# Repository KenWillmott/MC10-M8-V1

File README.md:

# MC10-M8-V1
Basic TRS-80 MC-10 to M8 expansion interface

## Description
Allows one M8 peripheral expansion card to operate from the expansion port on the rear of the TRS-80 MC-10 microcomputer. The circuit decodes an I/O slot at 0xB400-0xB7FF, so any M8 peripheral card will be addressed by the MC-10 at that location, plus any internal offset that the card uses. In order to prevent a hardware bus conflict when accessing those location, the SEL line on the MC-10 interface is activated to disable its internal devices mapped to the same locations.

Note: Gating with the CPU E signal is not performed by the interface card, it is always done on the M8 card. But, this is quite easy to do on the M8 card and some cards can do it without additional logic, since some I/O IC's perform E gating internally (such as 6522 VIA, Motorola MC6850, MC6821 etc.).

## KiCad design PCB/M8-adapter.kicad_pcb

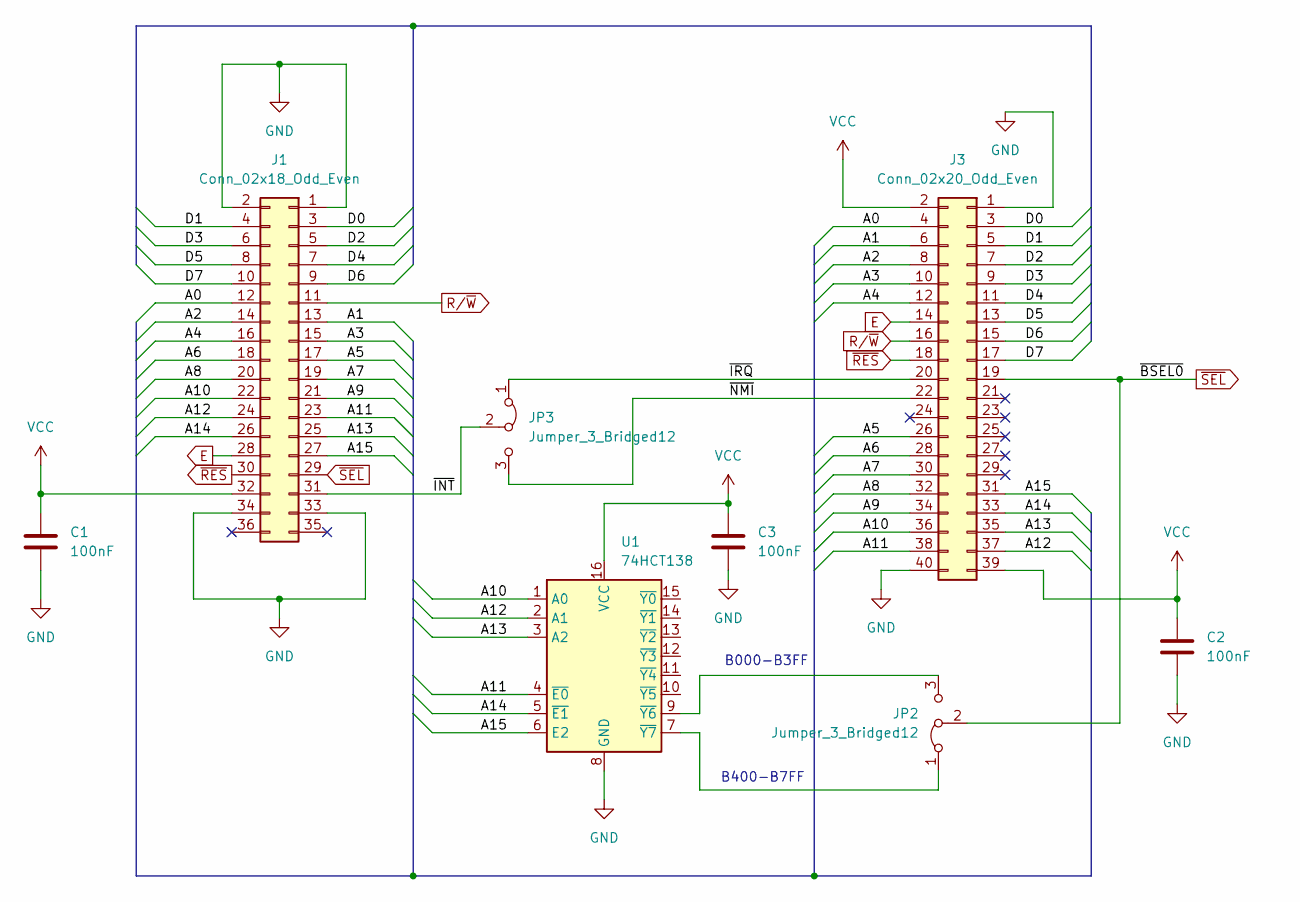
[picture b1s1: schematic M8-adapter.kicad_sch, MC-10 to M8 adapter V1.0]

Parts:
C1, C2, C3: 100nF; C_Disc_D5.0mm_W2.5mm_P5.00mm
J1: Conn_02x18_Odd_Even; Edge_Conn_2x18_P2.54mm_RA
J3: Conn_02x20_Odd_Even; PinSocket_2x20_P2.54mm_Vertical
JP2, JP3: Jumper_3_Bridged12; SolderJumper-3_P1.3mm_Bridged12_RoundedPad1.0x1.5mm
U1: 74HCT138; DIP-16_W7.62mm_LongPads

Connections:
/A0: J1.12, J3.4
/A1: J1.13, J3.6
/A2: J1.14, J3.8
/A3: J1.15, J3.10
/A4: J1.16, J3.12
/A5: J1.17, J3.26
/A6: J1.18, J3.28
/A7: J1.19, J3.30
/A8: J1.20, J3.32
/A9: J1.21, J3.34
/A10: J1.22, J3.36, U1.1 (A0)
/A11: J1.23, J3.38, U1.4 (~E0)
/A12: J1.24, J3.37, U1.2 (A1)
/A13: J1.25, J3.35, U1.3 (A2)
/A14: J1.26, J3.33, U1.5 (~E1)
/A15: J1.27, J3.31, U1.6 (E2)
/D0: J1.3, J3.3
/D1: J1.4, J3.5
/D2: J1.5, J3.7
/D3: J1.6, J3.9
/D4: J1.7, J3.11
/D5: J1.8, J3.13
/D6: J1.9, J3.15
/D7: J1.10, J3.17
/~INT: J1.31, JP3.2 (C)
/~IRQ: J3.20, JP3.1 (A)
/~NMI: J3.22, JP3.3 (B)
E: J1.28, J3.14
GND: C1.2, C2.2, C3.2, J1.1, J1.2, J1.33, J1.34, J3.1, J3.40, U1.8 (GND)
unnamed: JP2.1 (A), U1.7 (~Y7)
unnamed: JP2.3 (B), U1.9 (~Y6)
R/~W: J1.11, J3.16
VCC: C1.1, C2.1, C3.1, J1.32, J3.2, J3.39, U1.16 (VCC)
~RES: J1.30, J3.18
~SEL: J1.29, J3.19, JP2.2 (C)

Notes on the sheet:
B400-B7FF
B000-B3FF

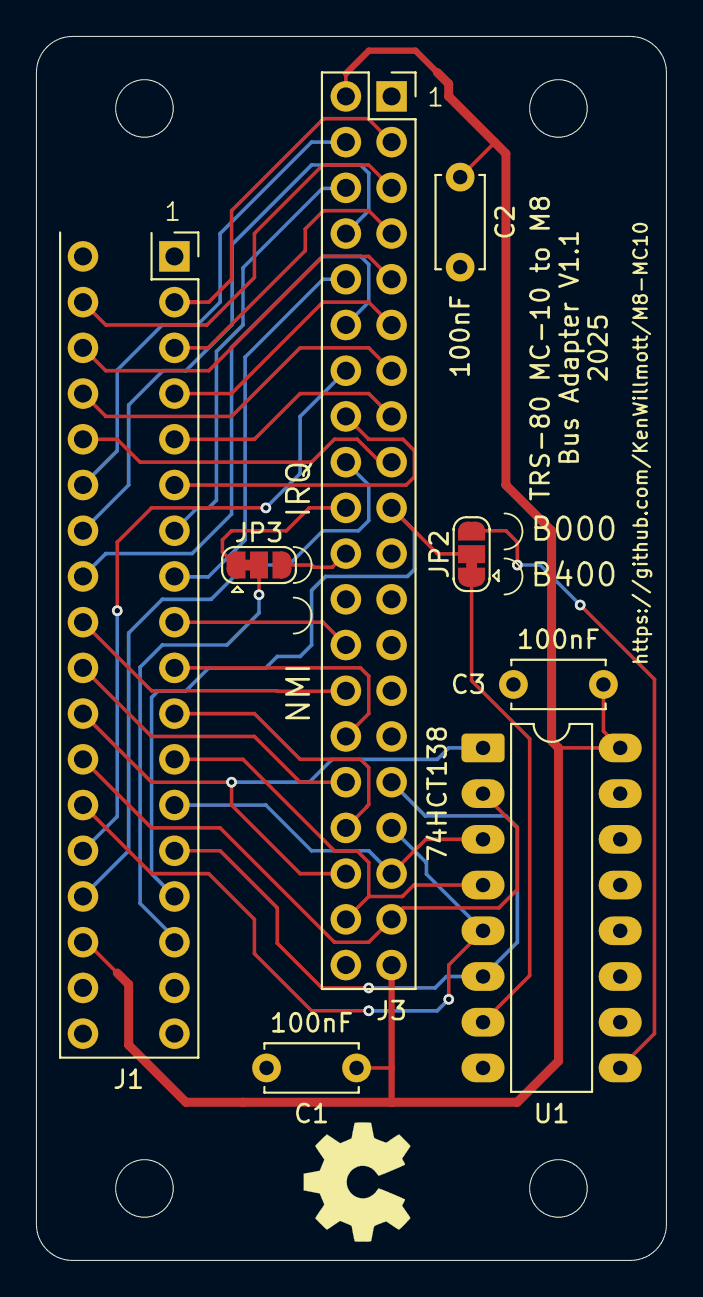
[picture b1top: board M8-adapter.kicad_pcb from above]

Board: 2 copper layers, 35.0 x 68.0 mm, 8 parts (0 on the bottom side), 35 nets.

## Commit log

2025-04-15 schematic
2025-04-15 Create foo
2025-04-15 board preview
2025-04-15 Gerbers
